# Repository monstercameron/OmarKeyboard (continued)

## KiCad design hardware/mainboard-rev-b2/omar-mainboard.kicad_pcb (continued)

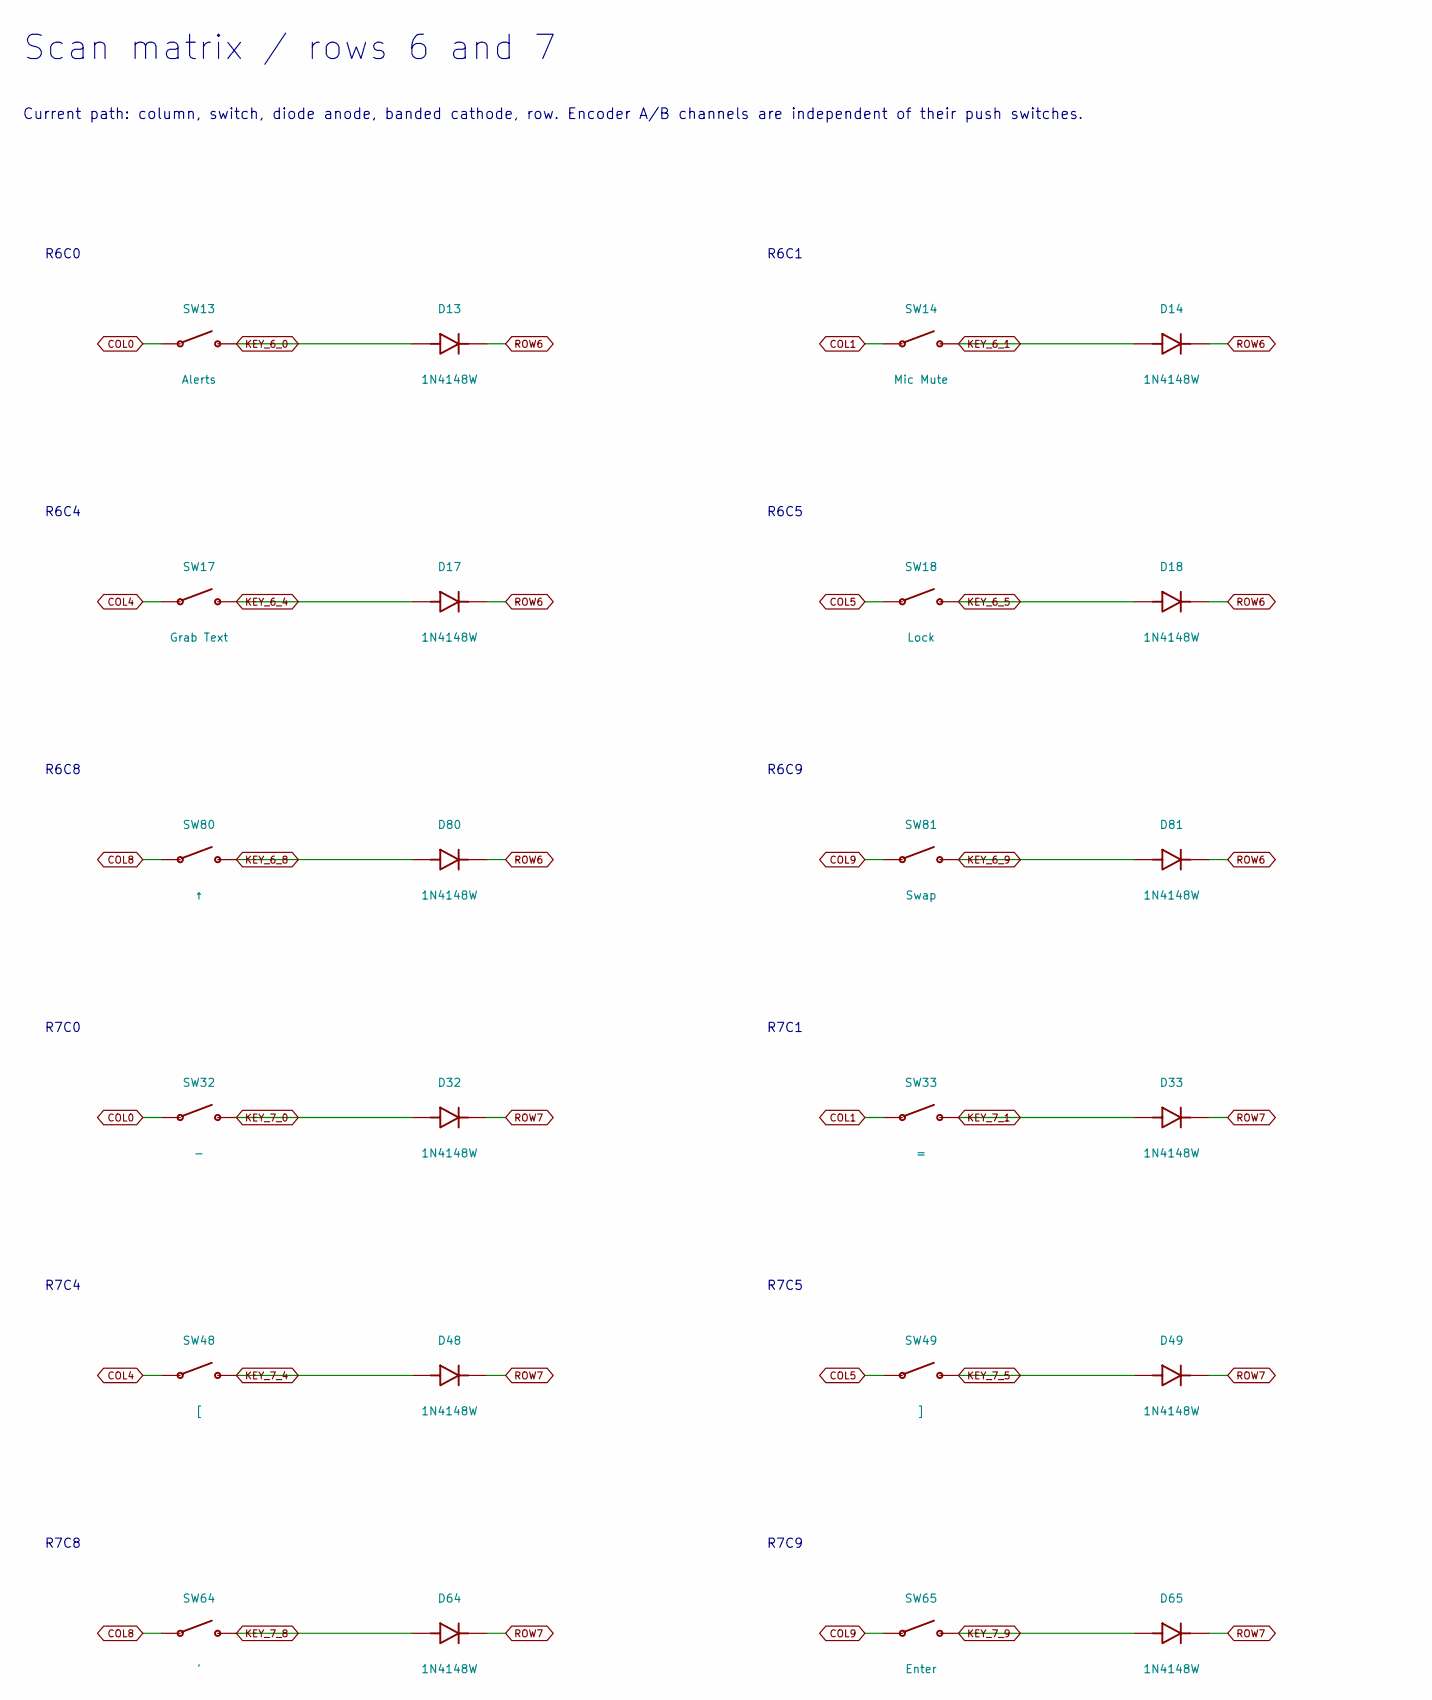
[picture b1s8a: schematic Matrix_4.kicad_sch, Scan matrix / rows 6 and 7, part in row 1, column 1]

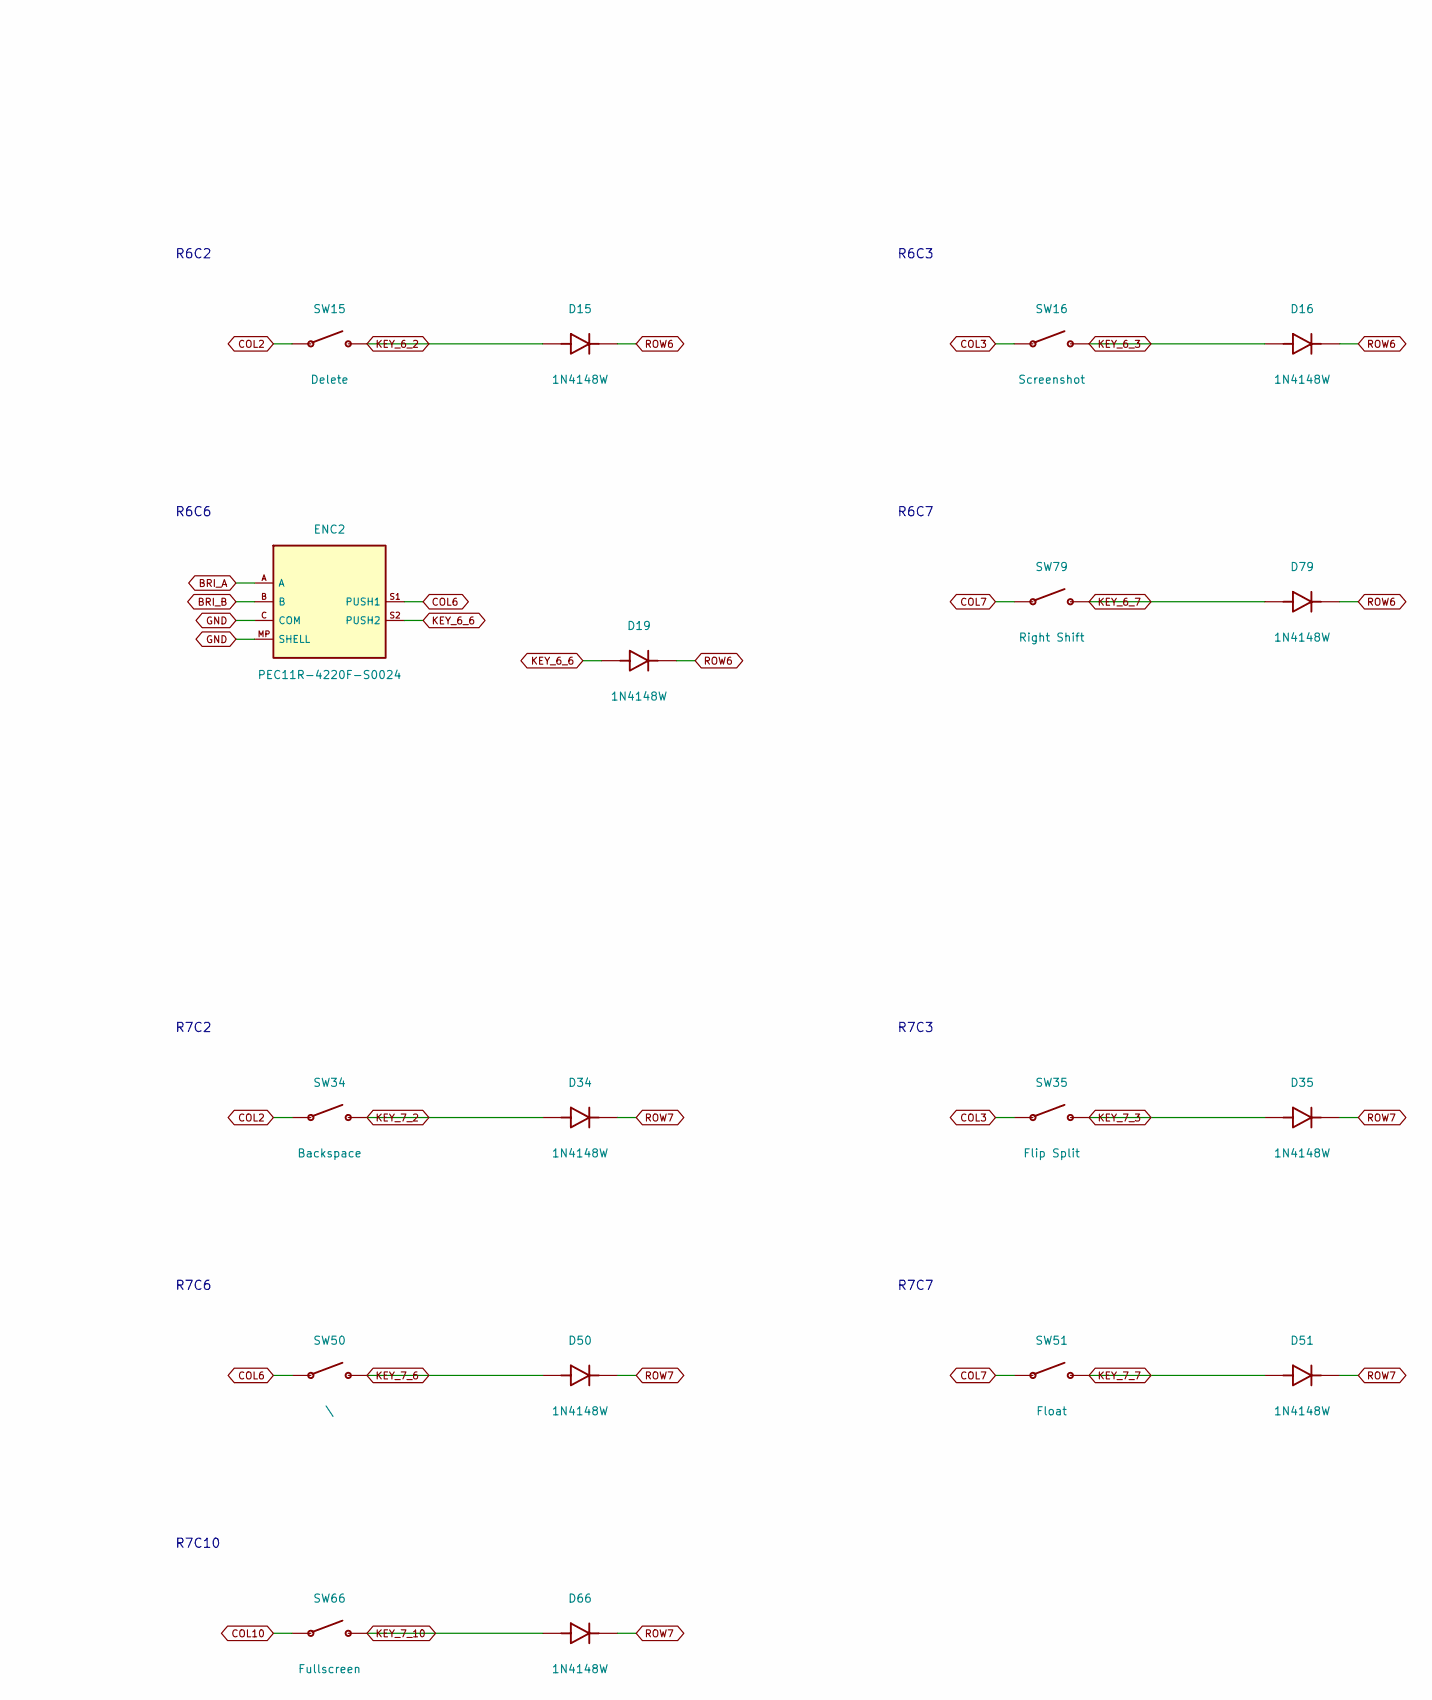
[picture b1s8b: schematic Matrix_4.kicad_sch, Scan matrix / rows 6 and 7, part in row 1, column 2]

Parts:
D13, D14, D15, D16, D17, D18, D19, D32, D33, D34, D35, D48, D49, D50, D51, D64, D65, D66, D79, D80, D81: 1N4148W; D_SOD-123
ENC2: PEC11R-4220F-S0024; PEC11R_4xxxF_S
SW13: Alerts; MX_Hotswap_North
SW14: Mic Mute; MX_Hotswap_North
SW15: Delete; MX_Hotswap_North
SW16: Screenshot; MX_Hotswap_North
SW17: Grab Text; MX_Hotswap_North
SW18: Lock; MX_Hotswap_North
SW32: -; MX_Hotswap_North
SW33: =; MX_Hotswap_North
SW34: Backspace; MX_Hotswap_North
SW35: Flip Split; MX_Hotswap_North
SW48: [; MX_Hotswap_North
SW49: ]; MX_Hotswap_North
SW50: \; MX_Hotswap_North
SW51: Float; MX_Hotswap_North
SW64: '; MX_Hotswap_North
SW65: Enter; MX_Hotswap_North
SW66: Fullscreen; MX_Hotswap_North
SW79: Right Shift; MX_Hotswap_North
SW80: ↑; MX_Hotswap_North
SW81: Swap; MX_Hotswap_North

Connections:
BRI_A: ENC2.A; also elsewhere on the board
BRI_B: ENC2.B; also elsewhere on the board
COL0: SW13.1, SW32.1; also elsewhere on the board
COL1: SW14.1, SW33.1; also elsewhere on the board
COL2: SW15.1, SW34.1; also elsewhere on the board
COL3: SW16.1, SW35.1; also elsewhere on the board
COL4: SW17.1, SW48.1; also elsewhere on the board
COL5: SW18.1, SW49.1; also elsewhere on the board
COL6: ENC2.S1 (PUSH1), SW50.1; also elsewhere on the board
COL7: SW51.1, SW79.1; also elsewhere on the board
COL8: SW64.1, SW80.1; also elsewhere on the board
COL9: SW65.1, SW81.1; also elsewhere on the board
COL10: SW66.1; also elsewhere on the board
GND: ENC2.C (COM), ENC2.MP (SHELL); also elsewhere on the board
KEY_6_0: D13.2 (A), SW13.2
KEY_6_1: D14.2 (A), SW14.2
KEY_6_2: D15.2 (A), SW15.2
KEY_6_3: D16.2 (A), SW16.2
KEY_6_4: D17.2 (A), SW17.2
KEY_6_5: D18.2 (A), SW18.2
KEY_6_6: D19.2 (A), ENC2.S2 (PUSH2)
KEY_6_7: D79.2 (A), SW79.2
KEY_6_8: D80.2 (A), SW80.2
KEY_6_9: D81.2 (A), SW81.2
KEY_7_0: D32.2 (A), SW32.2
KEY_7_1: D33.2 (A), SW33.2
KEY_7_2: D34.2 (A), SW34.2
KEY_7_3: D35.2 (A), SW35.2
KEY_7_4: D48.2 (A), SW48.2
KEY_7_5: D49.2 (A), SW49.2
KEY_7_6: D50.2 (A), SW50.2
KEY_7_7: D51.2 (A), SW51.2
KEY_7_8: D64.2 (A), SW64.2
KEY_7_9: D65.2 (A), SW65.2
KEY_7_10: D66.2 (A), SW66.2
ROW6: D13.1 (K), D14.1 (K), D15.1 (K), D16.1 (K), D17.1 (K), D18.1 (K), D19.1 (K), D79.1 (K), D80.1 (K), D81.1 (K); also elsewhere on the board
ROW7: D32.1 (K), D33.1 (K), D34.1 (K), D35.1 (K), D48.1 (K), D49.1 (K), D50.1 (K), D51.1 (K), D64.1 (K), D65.1 (K), D66.1 (K); also elsewhere on the board

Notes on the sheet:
Scan matrix / rows 6 and 7
Current path: column, switch, diode anode, banded cathode, row. Encoder A/B channels are independent of their push switches.
R6C0
R6C1
R6C2
R6C3
R6C4
R6C5
R6C6
R7C0
R7C1
R7C2
R7C3
R7C4
R7C5
R7C6
R7C7
R7C8
R7C9
R7C10
R6C7
R6C8
R6C9

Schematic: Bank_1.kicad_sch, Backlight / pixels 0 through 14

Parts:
C102, C103, C104, C105, C106, C107, C108, C109, C116, C117, C118, C119, C120, C121, C122: 100n; C_0603_1608Metric
LED2, LED3, LED4, LED5, LED6, LED7, LED8, LED9, LED16, LED17, LED18, LED19, LED20, LED21, LED22: SK6812MINI-E; SK6812MINI_E_Rev02

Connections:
GND: C102.2, C103.2, C104.2, C105.2, C106.2, C107.2, C108.2, C109.2, C116.2, C117.2, C118.2, C119.2, C120.2, C121.2, C122.2, LED2.3 (GND), LED3.3 (GND), LED4.3 (GND), LED5.3 (GND), LED6.3 (GND), LED7.3 (GND), LED8.3 (GND), LED9.3 (GND), LED16.3 (GND), LED17.3 (GND), LED18.3 (GND), LED19.3 (GND), LED20.3 (GND), LED21.3 (GND), LED22.3 (GND); also elsewhere on the board
PIX0: LED16.4 (DIN); also elsewhere on the board
PIX1: LED2.4 (DIN), LED16.2 (DOUT)
PIX2: LED2.2 (DOUT), LED3.4 (DIN)
PIX3: LED3.2 (DOUT), LED4.4 (DIN)
PIX4: LED4.2 (DOUT), LED5.4 (DIN)
PIX5: LED5.2 (DOUT), LED6.4 (DIN)
PIX6: LED6.2 (DOUT), LED17.4 (DIN)
PIX7: LED7.4 (DIN), LED17.2 (DOUT)
PIX8: LED7.2 (DOUT), LED8.4 (DIN)
PIX9: LED8.2 (DOUT), LED18.4 (DIN)
PIX10: LED18.2 (DOUT), LED19.4 (DIN)
PIX11: LED19.2 (DOUT), LED20.4 (DIN)
PIX12: LED9.4 (DIN), LED20.2 (DOUT)
PIX13: LED9.2 (DOUT), LED21.4 (DIN)
PIX14: LED21.2 (DOUT), LED22.4 (DIN)
PIX15: LED22.2 (DOUT); also elsewhere on the board
VLED: C102.1, C103.1, C104.1, C105.1, C106.1, C107.1, C108.1, C109.1, C116.1, C117.1, C118.1, C119.1, C120.1, C121.1, C122.1, LED2.1 (VDD), LED3.1 (VDD), LED4.1 (VDD), LED5.1 (VDD), LED6.1 (VDD), LED7.1 (VDD), LED8.1 (VDD), LED9.1 (VDD), LED16.1 (VDD), LED17.1 (VDD), LED18.1 (VDD), LED19.1 (VDD), LED20.1 (VDD), LED21.1 (VDD), LED22.1 (VDD); also elsewhere on the board

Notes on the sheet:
Backlight / pixels 0 through 14
Board view from above. Every emitter has a local 100 nF bypass. Data flows from DIN to DOUT in index order.
0 Esc
1 Desk 1
2 Desk 2
3 Desk 3
4 Desk 4
5 Desk 5
6 Last Desk
7 Send & Stay
8 Move & Go
9 Clipboard
10 Paste
11 Alerts
12 Mic Mute
13 Delete
14 Screenshot

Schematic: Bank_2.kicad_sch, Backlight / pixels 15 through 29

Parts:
C123, C124, C128, C129, C130, C131, C132, C133, C134, C135, C136, C137, C138, C139, C140: 100n; C_0603_1608Metric
LED23, LED24, LED28, LED29, LED30, LED31, LED32, LED33, LED34, LED35, LED36, LED37, LED38, LED39, LED40: SK6812MINI-E; SK6812MINI_E_Rev02

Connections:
GND: C123.2, C124.2, C128.2, C129.2, C130.2, C131.2, C132.2, C133.2, C134.2, C135.2, C136.2, C137.2, C138.2, C139.2, C140.2, LED23.3 (GND), LED24.3 (GND), LED28.3 (GND), LED29.3 (GND), LED30.3 (GND), LED31.3 (GND), LED32.3 (GND), LED33.3 (GND), LED34.3 (GND), LED35.3 (GND), LED36.3 (GND), LED37.3 (GND), LED38.3 (GND), LED39.3 (GND), LED40.3 (GND); also elsewhere on the board
PIX15: LED23.4 (DIN); also elsewhere on the board
PIX16: LED23.2 (DOUT), LED24.4 (DIN)
PIX17: LED24.2 (DOUT), LED40.4 (DIN)
PIX18: LED39.4 (DIN), LED40.2 (DOUT)
PIX19: LED38.4 (DIN), LED39.2 (DOUT)
PIX20: LED37.4 (DIN), LED38.2 (DOUT)
PIX21: LED36.4 (DIN), LED37.2 (DOUT)
PIX22: LED35.4 (DIN), LED36.2 (DOUT)
PIX23: LED34.4 (DIN), LED35.2 (DOUT)
PIX24: LED33.4 (DIN), LED34.2 (DOUT)
PIX25: LED32.4 (DIN), LED33.2 (DOUT)
PIX26: LED31.4 (DIN), LED32.2 (DOUT)
PIX27: LED30.4 (DIN), LED31.2 (DOUT)
PIX28: LED29.4 (DIN), LED30.2 (DOUT)
PIX29: LED28.4 (DIN), LED29.2 (DOUT)
PIX30: LED28.2 (DOUT); also elsewhere on the board
VLED: C123.1, C124.1, C128.1, C129.1, C130.1, C131.1, C132.1, C133.1, C134.1, C135.1, C136.1, C137.1, C138.1, C139.1, C140.1, LED23.1 (VDD), LED24.1 (VDD), LED28.1 (VDD), LED29.1 (VDD), LED30.1 (VDD), LED31.1 (VDD), LED32.1 (VDD), LED33.1 (VDD), LED34.1 (VDD), LED35.1 (VDD), LED36.1 (VDD), LED37.1 (VDD), LED38.1 (VDD), LED39.1 (VDD), LED40.1 (VDD); also elsewhere on the board

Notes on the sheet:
Backlight / pixels 15 through 29
Board view from above. Every emitter has a local 100 nF bypass. Data flows from DIN to DOUT in index order.
15 Grab Text
16 Lock
17 Flip Split
18 Backspace
19 =
20 -
21 0
22 9
23 8
24 7
25 6
26 5
27 4
28 3
29 2

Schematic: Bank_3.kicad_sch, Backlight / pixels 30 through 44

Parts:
C125, C126, C127, C141, C142, C143, C144, C145, C146, C147, C148, C149, C150, C151, C152: 100n; C_0603_1608Metric
LED25, LED26, LED27, LED41, LED42, LED43, LED44, LED45, LED46, LED47, LED48, LED49, LED50, LED51, LED52: SK6812MINI-E; SK6812MINI_E_Rev02

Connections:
GND: C125.2, C126.2, C127.2, C141.2, C142.2, C143.2, C144.2, C145.2, C146.2, C147.2, C148.2, C149.2, C150.2, C151.2, C152.2, LED25.3 (GND), LED26.3 (GND), LED27.3 (GND), LED41.3 (GND), LED42.3 (GND), LED43.3 (GND), LED44.3 (GND), LED45.3 (GND), LED46.3 (GND), LED47.3 (GND), LED48.3 (GND), LED49.3 (GND), LED50.3 (GND), LED51.3 (GND), LED52.3 (GND); also elsewhere on the board
PIX30: LED27.4 (DIN); also elsewhere on the board
PIX31: LED26.4 (DIN), LED27.2 (DOUT)
PIX32: LED25.4 (DIN), LED26.2 (DOUT)
PIX33: LED25.2 (DOUT), LED41.4 (DIN)
PIX34: LED41.2 (DOUT), LED42.4 (DIN)
PIX35: LED42.2 (DOUT), LED43.4 (DIN)
PIX36: LED43.2 (DOUT), LED44.4 (DIN)
PIX37: LED44.2 (DOUT), LED45.4 (DIN)
PIX38: LED45.2 (DOUT), LED46.4 (DIN)
PIX39: LED46.2 (DOUT), LED47.4 (DIN)
PIX40: LED47.2 (DOUT), LED48.4 (DIN)
PIX41: LED48.2 (DOUT), LED49.4 (DIN)
PIX42: LED49.2 (DOUT), LED50.4 (DIN)
PIX43: LED50.2 (DOUT), LED51.4 (DIN)
PIX44: LED51.2 (DOUT), LED52.4 (DIN)
PIX45: LED52.2 (DOUT); also elsewhere on the board
VLED: C125.1, C126.1, C127.1, C141.1, C142.1, C143.1, C144.1, C145.1, C146.1, C147.1, C148.1, C149.1, C150.1, C151.1, C152.1, LED25.1 (VDD), LED26.1 (VDD), LED27.1 (VDD), LED41.1 (VDD), LED42.1 (VDD), LED43.1 (VDD), LED44.1 (VDD), LED45.1 (VDD), LED46.1 (VDD), LED47.1 (VDD), LED48.1 (VDD), LED49.1 (VDD), LED50.1 (VDD), LED51.1 (VDD), LED52.1 (VDD); also elsewhere on the board

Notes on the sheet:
Backlight / pixels 30 through 44
Board view from above. Every emitter has a local 100 nF bypass. Data flows from DIN to DOUT in index order.
30 1
31 ~
32 Guide
33 Browser
34 Tab
35 Q
36 W
37 E
38 R
39 T
40 Y
41 U
42 I
43 O
44 P

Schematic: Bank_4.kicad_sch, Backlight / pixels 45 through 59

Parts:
C153, C154, C155, C156, C160, C161, C162, C163, C164, C165, C166, C167, C168, C169, C170: 100n; C_0603_1608Metric
LED53, LED54, LED55, LED56, LED60, LED61, LED62, LED63, LED64, LED65, LED66, LED67, LED68, LED69, LED70: SK6812MINI-E; SK6812MINI_E_Rev02

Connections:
GND: C153.2, C154.2, C155.2, C156.2, C160.2, C161.2, C162.2, C163.2, C164.2, C165.2, C166.2, C167.2, C168.2, C169.2, C170.2, LED53.3 (GND), LED54.3 (GND), LED55.3 (GND), LED56.3 (GND), LED60.3 (GND), LED61.3 (GND), LED62.3 (GND), LED63.3 (GND), LED64.3 (GND), LED65.3 (GND), LED66.3 (GND), LED67.3 (GND), LED68.3 (GND), LED69.3 (GND), LED70.3 (GND); also elsewhere on the board
PIX45: LED53.4 (DIN); also elsewhere on the board
PIX46: LED53.2 (DOUT), LED54.4 (DIN)
PIX47: LED54.2 (DOUT), LED55.4 (DIN)
PIX48: LED55.2 (DOUT), LED56.4 (DIN)
PIX49: LED56.2 (DOUT), LED70.4 (DIN)
PIX50: LED69.4 (DIN), LED70.2 (DOUT)
PIX51: LED68.4 (DIN), LED69.2 (DOUT)
PIX52: LED67.4 (DIN), LED68.2 (DOUT)
PIX53: LED66.4 (DIN), LED67.2 (DOUT)
PIX54: LED65.4 (DIN), LED66.2 (DOUT)
PIX55: LED64.4 (DIN), LED65.2 (DOUT)
PIX56: LED63.4 (DIN), LED64.2 (DOUT)
PIX57: LED62.4 (DIN), LED63.2 (DOUT)
PIX58: LED61.4 (DIN), LED62.2 (DOUT)
PIX59: LED60.4 (DIN), LED61.2 (DOUT)
PIX60: LED60.2 (DOUT); also elsewhere on the board
VLED: C153.1, C154.1, C155.1, C156.1, C160.1, C161.1, C162.1, C163.1, C164.1, C165.1, C166.1, C167.1, C168.1, C169.1, C170.1, LED53.1 (VDD), LED54.1 (VDD), LED55.1 (VDD), LED56.1 (VDD), LED60.1 (VDD), LED61.1 (VDD), LED62.1 (VDD), LED63.1 (VDD), LED64.1 (VDD), LED65.1 (VDD), LED66.1 (VDD), LED67.1 (VDD), LED68.1 (VDD), LED69.1 (VDD), LED70.1 (VDD); also elsewhere on the board

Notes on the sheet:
Backlight / pixels 45 through 59
Board view from above. Every emitter has a local 100 nF bypass. Data flows from DIN to DOUT in index order.
45 [
46 ]
47 \
48 Float
49 Fullscreen
50 Enter
51 '
52 ;
53 L
54 K
55 J
56 H
57 G
58 F
59 D

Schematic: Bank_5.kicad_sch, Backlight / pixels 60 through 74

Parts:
C101, C157, C158, C159, C171, C172, C173, C174, C175, C176, C177, C178, C179, C180, C181: 100n; C_0603_1608Metric
LED1, LED57, LED58, LED59, LED71, LED72, LED73, LED74, LED75, LED76, LED77, LED78, LED79, LED80, LED81: SK6812MINI-E; SK6812MINI_E_Rev02

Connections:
GND: C101.2, C157.2, C158.2, C159.2, C171.2, C172.2, C173.2, C174.2, C175.2, C176.2, C177.2, C178.2, C179.2, C180.2, C181.2, LED1.3 (GND), LED57.3 (GND), LED58.3 (GND), LED59.3 (GND), LED71.3 (GND), LED72.3 (GND), LED73.3 (GND), LED74.3 (GND), LED75.3 (GND), LED76.3 (GND), LED77.3 (GND), LED78.3 (GND), LED79.3 (GND), LED80.3 (GND), LED81.3 (GND); also elsewhere on the board
PIX60: LED59.4 (DIN); also elsewhere on the board
PIX61: LED58.4 (DIN), LED59.2 (DOUT)
PIX62: LED1.4 (DIN), LED58.2 (DOUT)
PIX63: LED1.2 (DOUT), LED57.4 (DIN)
PIX64: LED57.2 (DOUT), LED71.4 (DIN)
PIX65: LED71.2 (DOUT), LED72.4 (DIN)
PIX66: LED72.2 (DOUT), LED73.4 (DIN)
PIX67: LED73.2 (DOUT), LED74.4 (DIN)
PIX68: LED74.2 (DOUT), LED75.4 (DIN)
PIX69: LED75.2 (DOUT), LED76.4 (DIN)
PIX70: LED76.2 (DOUT), LED77.4 (DIN)
PIX71: LED77.2 (DOUT), LED78.4 (DIN)
PIX72: LED78.2 (DOUT), LED79.4 (DIN)
PIX73: LED79.2 (DOUT), LED80.4 (DIN)
PIX74: LED80.2 (DOUT), LED81.4 (DIN)
PIX75: LED81.2 (DOUT); also elsewhere on the board
VLED: C101.1, C157.1, C158.1, C159.1, C171.1, C172.1, C173.1, C174.1, C175.1, C176.1, C177.1, C178.1, C179.1, C180.1, C181.1, LED1.1 (VDD), LED57.1 (VDD), LED58.1 (VDD), LED59.1 (VDD), LED71.1 (VDD), LED72.1 (VDD), LED73.1 (VDD), LED74.1 (VDD), LED75.1 (VDD), LED76.1 (VDD), LED77.1 (VDD), LED78.1 (VDD), LED79.1 (VDD), LED80.1 (VDD), LED81.1 (VDD); also elsewhere on the board

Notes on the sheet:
Backlight / pixels 60 through 74
Board view from above. Every emitter has a local 100 nF bypass. Data flows from DIN to DOUT in index order.
60 S
61 A
62 Caps
63 Menu
64 Terminal
65 Left Shift
66 Z
67 X
68 C
69 V
70 B
71 N
72 M
73 ,
74 .

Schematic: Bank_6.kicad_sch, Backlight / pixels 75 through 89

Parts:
C110, C111, C112, C113, C114, C115, C182, C183, C184, C185, C186, C187, C188, C189, C190: 100n; C_0603_1608Metric
LED10, LED11, LED12, LED13, LED14, LED15, LED82, LED83, LED84, LED85, LED86, LED87, LED88, LED89, LED90: SK6812MINI-E; SK6812MINI_E_Rev02

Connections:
GND: C110.2, C111.2, C112.2, C113.2, C114.2, C115.2, C182.2, C183.2, C184.2, C185.2, C186.2, C187.2, C188.2, C189.2, C190.2, LED10.3 (GND), LED11.3 (GND), LED12.3 (GND), LED13.3 (GND), LED14.3 (GND), LED15.3 (GND), LED82.3 (GND), LED83.3 (GND), LED84.3 (GND), LED85.3 (GND), LED86.3 (GND), LED87.3 (GND), LED88.3 (GND), LED89.3 (GND), LED90.3 (GND); also elsewhere on the board
LED_OUT: LED84.2 (DOUT); also elsewhere on the board
PIX75: LED82.4 (DIN); also elsewhere on the board
PIX76: LED82.2 (DOUT), LED83.4 (DIN)
PIX77: LED15.4 (DIN), LED83.2 (DOUT)
PIX78: LED10.4 (DIN), LED15.2 (DOUT)
PIX79: LED10.2 (DOUT), LED11.4 (DIN)
PIX80: LED11.2 (DOUT), LED12.4 (DIN)
PIX81: LED12.2 (DOUT), LED13.4 (DIN)
PIX82: LED13.2 (DOUT), LED14.4 (DIN)
PIX83: LED14.2 (DOUT), LED90.4 (DIN)
PIX84: LED89.4 (DIN), LED90.2 (DOUT)
PIX85: LED88.4 (DIN), LED89.2 (DOUT)
PIX86: LED87.4 (DIN), LED88.2 (DOUT)
PIX87: LED86.4 (DIN), LED87.2 (DOUT)
PIX88: LED85.4 (DIN), LED86.2 (DOUT)
PIX89: LED84.4 (DIN), LED85.2 (DOUT)
VLED: C110.1, C111.1, C112.1, C113.1, C114.1, C115.1, C182.1, C183.1, C184.1, C185.1, C186.1, C187.1, C188.1, C189.1, C190.1, LED10.1 (VDD), LED11.1 (VDD), LED12.1 (VDD), LED13.1 (VDD), LED14.1 (VDD), LED15.1 (VDD), LED82.1 (VDD), LED83.1 (VDD), LED84.1 (VDD), LED85.1 (VDD), LED86.1 (VDD), LED87.1 (VDD), LED88.1 (VDD), LED89.1 (VDD), LED90.1 (VDD); also elsewhere on the board

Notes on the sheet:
Backlight / pixels 75 through 89
Board view from above. Every emitter has a local 100 nF bypass. Data flows from DIN to DOUT in index order.
75 /
76 Right Shift
77 ↑
78 Swap
79 Focus
80 →
81 ↓
82 ←
83 Right Ctrl
84 Next Window
85 Right Super
86 Space
87 Left Super
88 Ctrl
89 Files

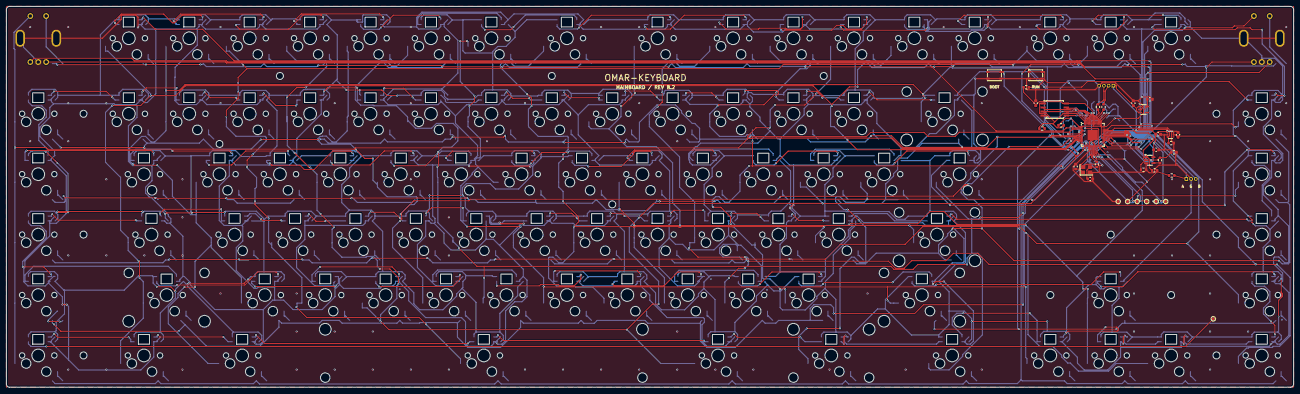
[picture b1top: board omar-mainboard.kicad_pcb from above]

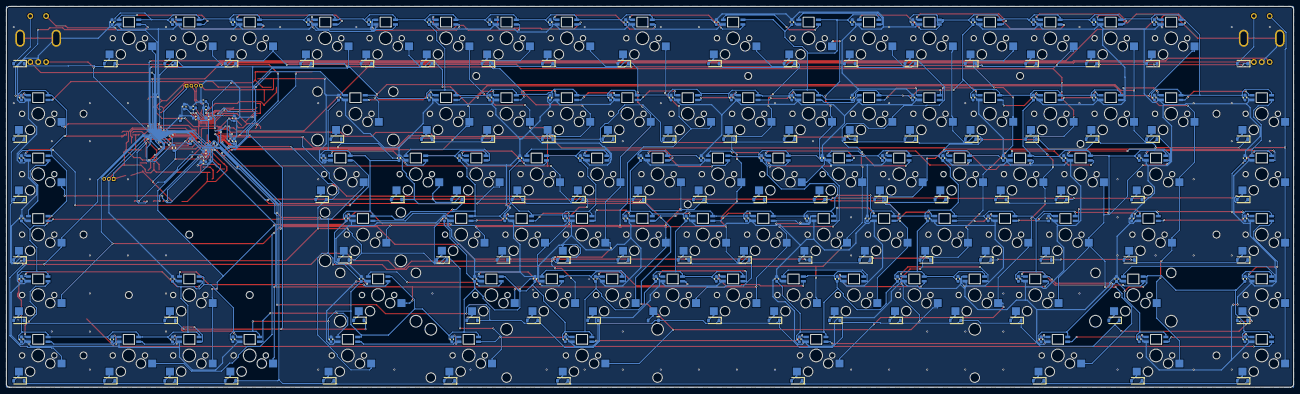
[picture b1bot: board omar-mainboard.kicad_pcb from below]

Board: 2 copper layers, 405.8 x 120.1 mm, 452 parts (375 on the bottom side), 235 nets.

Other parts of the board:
H1, H2, H3, H4, H5, H6, H7, H8, H9, H10, H11, H12: M2 shared; NPTH_2p2
H13, H14: M2 proposed; NPTH_2p2
HS1, HS3, HS5, HS7, HS9, HS11, HS13, HS15, HS17, HS19, HS21, HS23: Stabilizer; NPTH_3p0
HS2, HS4, HS6, HS8, HS10, HS12, HS14, HS16, HS18, HS20, HS22, HS24: Stabilizer; NPTH_3p7

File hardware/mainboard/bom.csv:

Quantity,Value_or_part,Footprint,PCB_side,References
3,1u,Capacitor_SMD:C_0603_1608Metric,F,C1 C2 C17
2,1u,Capacitor_SMD:C_0603_1608Metric,B,C3 C4
25,100n,Capacitor_SMD:C_0603_1608Metric,B,C5 C6 C7 C8 C9 C10 C11 C12 C18 C19 C101 C102 C103 C104 C105 C106 C107 C108 C109 C110 C111 C112 C113 C114 C115
2,100n,Capacitor_SMD:C_0603_1608Metric,F,C13 C16
2,15p,Capacitor_SMD:C_0603_1608Metric,F,C14 C15
91,1N4148W,Diode_SMD:D_SOD-123,B,D1 D2 D3 D4 D5 D6 D7 D8 D9 D10 D11 D12 D13 D14 D15 D16 D17 D18 D19 D20 D21 D22 D23 D24 D25 D26 D27 D28 D29 D30 D31 D32 D33 D34 D35 D36 D37 D38 D39 D40 D41 D42 D43 D44 D45 D46 D47 D48 D49 D50 D51 D52 D53 D54 D55 D56 D57 D58 D59 D60 D61 D62 D63 D64 D65 D66 D67 D68 D69 D70 D71 D72 D73 D74 D76 D77 D78 D79 D80 D81 D82 D83 D84 D85 D86 D87 D88 D89 D90 D91 D92
1,1N4148W,Omar:D_SOD123_Stabilizer_Clearance,B,D75
2,EN11-HSM1BF20,Omar:EN11_HSM,F,ENC1 ENC2
1,USB carrier / solder link,Omar:Wire_4_P1.5,F,J1
1,Roller A COM B,Omar:Wire_3_P1.5,F,J2
15,SK6812MINI-E,Omar:SK6812MINI_E_Rev02,B,LED1 LED2 LED3 LED4 LED5 LED6 LED7 LED8 LED9 LED10 LED11 LED12 LED13 LED14 LED15
2,27R,Resistor_SMD:R_0603_1608Metric,F,R1 R2
2,1k,Resistor_SMD:R_0603_1608Metric,F,R3 R5
2,10k,Resistor_SMD:R_0603_1608Metric,F,R4 R6
1,330R,Resistor_SMD:R_0603_1608Metric,F,R7
1,100k,Resistor_SMD:R_0603_1608Metric,F,R8
90,CPG151101S11-16,Omar:MX_Hotswap_North,B,SW2 SW3 SW4 SW5 SW6 SW7 SW8 SW9 SW10 SW11 SW12 SW13 SW14 SW15 SW16 SW17 SW18 SW20 SW21 SW22 SW23 SW24 SW25 SW26 SW27 SW28 SW29 SW30 SW31 SW32 SW33 SW34 SW35 SW36 SW37 SW38 SW39 SW40 SW41 SW42 SW43 SW44 SW45 SW46 SW47 SW48 SW49 SW50 SW51 SW52 SW53 SW54 SW55 SW56 SW57 SW58 SW59 SW60 SW61 SW62 SW63 SW64 SW65 SW66 SW67 SW68 SW69 SW70 SW71 SW72 SW73 SW74 SW75 SW76 SW77 SW78 SW79 SW80 SW81 SW82 SW83 SW84 SW85 SW86 SW87 SW88 SW89 SW90 SW91 SW92
1,BOOTSEL,Button_Switch_SMD:SW_SPST_PTS810,F,SW93
1,RESET,Button_Switch_SMD:SW_SPST_PTS810,F,SW94
1,GND,TestPoint:TestPoint_Pad_D1.0mm,F,TP1
1,+3V3,TestPoint:TestPoint_Pad_D1.0mm,F,TP2
1,SWCLK,TestPoint:TestPoint_Pad_D1.0mm,F,TP3
1,SWDIO,TestPoint:TestPoint_Pad_D1.0mm,F,TP4
1,+5V,TestPoint:TestPoint_Pad_D1.0mm,F,TP5
1,+1V1,TestPoint:TestPoint_Pad_D1.0mm,F,TP6
1,LED_OUT,TestPoint:TestPoint_Pad_D1.0mm,F,TP7
1,RP2040,Package_DFN_QFN:QFN-56-1EP_7x7mm_P0.4mm_EP3.2x3.2mm,F,U1
1,W25Q16JVSSIQ,Package_SO:SOIC-8W_5.3x5.3mm_P1.27mm,F,U2
1,AP2112K-3.3,Package_TO_SOT_SMD:SOT-23-5,F,U3
1,SN74AHCT1G125,Package_TO_SOT_SMD:SOT-23-5,F,U4
1,ABM8-272-T3 / 12 MHz,Crystal:Crystal_SMD_3225-4Pin_3.2x2.5mm,F,Y1

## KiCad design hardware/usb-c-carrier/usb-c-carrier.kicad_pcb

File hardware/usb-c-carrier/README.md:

# T4 USB-C carrier

A reversible USB 2.0 device inlet for the B.2 keyboard. J1 is the GCT USB4105-GF-A on the top face. The protection circuit and four hand-soldered harness lands occupy the underside.

| Fabrication input | File or specification |
| --- | --- |
| Bare PCB | [Gerbers, plated and non-plated Excellon drills, and Gerber job](usb-c-carrier-Gerbers.zip) |
| Editable source | [KiCad project](usb-c-carrier.kicad_pro), [schematic](usb-c-carrier.kicad_sch), [routed PCB](usb-c-carrier.kicad_pcb) |
| PCBA | [Manufacturer BOM](assembly-bom.csv) and [five assembly placements](placement.csv). J1 needs solder on its shell stakes. J2 is four integral lap pads. H1/H2 are bare mechanical holes. |
| CAD and verification | [Populated STEP](usb-c-carrier.step), [KiCad DRC](drc-report.txt) and [assembly specification, sheet 20](../assembly-design-specification.md) |
| Order notes | Finished 20 × 7 × 1.00 mm FR-4, four copper layers, 0.50 mm corner chamfers, 35 µm outer and nominal 17.5 µm inner copper. ENIG finish. Two-sided assembly. Ask the assembler to panelize this small outline. Keep tabs and tooling clear of the connector mouth. |
| Filled vias | [Fabrication notes and selective via coordinates](fabrication-notes.txt) are included in the bare-board ZIP. Specify planar plated-over epoxy-filled vias under the J1 A6 and B6 solder land ends at KiCad X100.25 and X99.25, both Y104.25. Finished holes Ø0.20 mm, lands Ø0.40 mm. Confirm the assembler’s via treatment before purchase. |
| Layout rules | 0.18 mm signal traces, 0.15 mm net clearance, 0.20 mm copper-to-edge and minimum hole clearance. The four coincident-ground designators A1/A12/B1/B12 use 0.60 × 1.11 mm lands. The locators, shell slots and contact centers follow the GCT footprint. |
| Results | 31 connected pin assignments match the schematic. Zero DRC violations, zero open connections and zero footprint errors. The STEP contains the board and five fitted parts. |

J1 A5 and B5 have independent 5.1 kΩ pull-downs. Both plug orientations share D+ and D−. U1 pin 2 goes to ground and pin 5 to raw VBUS. F1 feeds the cable. At J2 the pin order is 1 fused VBUS, 2 D−, 3 D+, 4 ground. Keep the differential pair twisted up to each breakout. The B.2 mainboard provides the two 27 Ω series resistors. A8 and B8 are unconnected.

The STEP origin is the J1 footprint center in plan and the PCB bottom in Z. In the keyboard STEP place the carrier at X95.25, Y+5.65, Z−6.55 mm. The placement CSV instead follows KiCad's unshifted manufacturing origin and uses negative board Y. Verify the assembler's rendered origins and part rotations against the PCB before approving assembly.

For the first article, measure the CC pull-downs and verify cable continuity and VBUS isolation with power off. Then power through a current-limited source, check the voltage at motherboard J1 and test enumeration and keyboard data in both plug orientations. Repeat at the firmware’s maximum allowed LED current and check fuse temperature, cable retention and plug insertion depth. The board has no measured USB signal-integrity or ESD qualification.

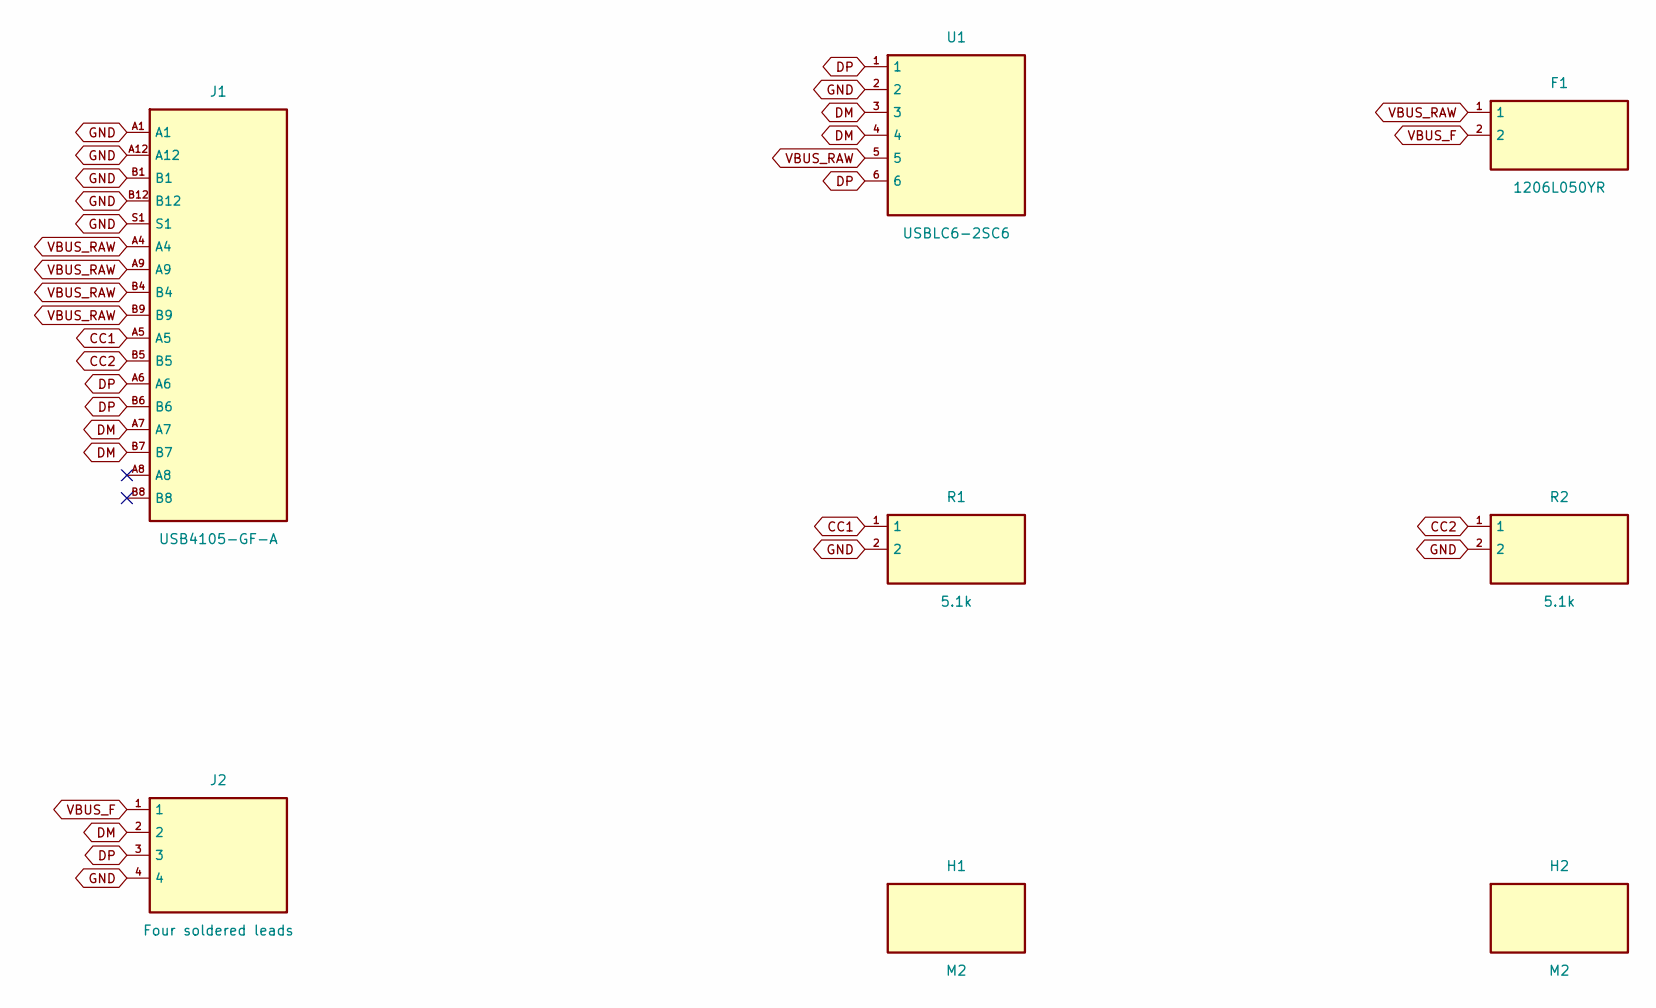
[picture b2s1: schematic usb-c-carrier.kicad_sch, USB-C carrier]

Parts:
F1: 1206L050YR; Fuse_1206_3216Metric
H1, H2: M2; Mount_M2
J1: USB4105-GF-A; USB_C_Receptacle_GCT_USB4105-xx-A_16P_TopMnt_Horizontal
J2: Four soldered leads; Harness4
R1, R2: 5.1k; R_0603_1608Metric
U1: USBLC6-2SC6; SOT-23-6

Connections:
CC1: J1.A5, R1.1
CC2: J1.B5, R2.1
DM: J1.A7, J1.B7, J2.2, U1.3, U1.4
DP: J1.A6, J1.B6, J2.3, U1.1, U1.6
GND: J1.A1, J1.A12, J1.B1, J1.B12, J1.S1, J2.4, R1.2, R2.2, U1.2
VBUS_F: F1.2, J2.1
VBUS_RAW: F1.1, J1.A4, J1.A9, J1.B4, J1.B9, U1.5

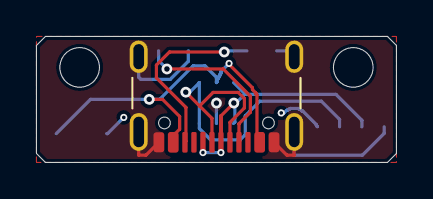
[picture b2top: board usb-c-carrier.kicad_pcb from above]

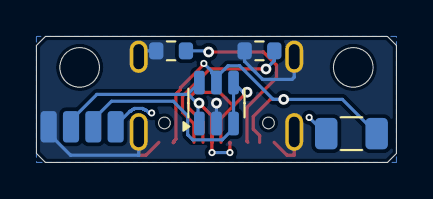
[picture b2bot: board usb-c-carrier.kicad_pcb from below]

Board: 4 copper layers, 20.0 x 7.0 mm, 8 parts (5 on the bottom side), 7 nets.

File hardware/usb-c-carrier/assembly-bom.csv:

Designator,Qty,Manufacturer,Manufacturer part number,Value / description,Mount
J1,1,GCT,USB4105-GF-A,"USB-C receptacle, 16-contact USB 2.0, hybrid SMT contacts and plated shell stakes",Top
U1,1,STMicroelectronics,USBLC6-2SC6,"Two-channel USB ESD array, SOT-23-6",Bottom
F1,1,Littelfuse,1206L050YR,"500 mA hold PPTC, 1206",Bottom
"R1,R2",2,YAGEO,RC0603FR-075K1L,"5.1 kΩ ±1%, 0603",Bottom
